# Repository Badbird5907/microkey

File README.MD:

# MicroKey
[Video Demo](https://youtube.com/shorts/Fg3U53FJ8HM)

Firmware can be found [here](https://github.com/Badbird5907/pico-fido-microkey)

This is a FIDO2 security key! It utilizes the RP2350A and [PicoKeys](https://picokeys.com) to implement FIDO2 U2F functionality! Unlike most picokeys, it uses a gold disc like the yubikey to detect touch instead of a tactile button.

I made this project because I saw the RP2350 could be used as a FIDO2 device with firmware like PicoKeys, and I couldn't find a yubikey-like device designed for PicoKeys. All the devices that were used were devboards, with tactile buttons and long USB cables.

# BOM
|Manufacturer                          |Description                                                                                                        |Quantity|Unit Price($)|Ext.Price($)|Link                                                                                                                                    |
|--------------------------------------|-------------------------------------------------------------------------------------------------------------------|--------|-------------|------------|----------------------------------------------------------------------------------------------------------------------------------------|
|UNI-ROYAL(Uniroyal Elec)              |62.5mW Thick Film Resistor 50V ±100ppm/℃ ±1% 1kΩ 0402 Chip Resistor - Surface Mount ROHS                           |100     |0.0006       |0.06        |https://lcsc.com/product-detail/chip-resistor-surface-mount_uni-royal-uniroyal-elec-0402wgf1001tce_C11702.html                          |
|Samsung Electro-Mechanics             |16V 100nF X7R ±10% 0402 Multilayer Ceramic Capacitors MLCC - SMD/SMT ROHS                                          |100     |0.0012       |0.12        |https://lcsc.com/product-detail/multilayer-ceramic-capacitors-mlcc-smd-smt_samsung-electro-mechanics-cl05b104ko5nnnc_C1525.html         |
|FH (Guangdong Fenghua Advanced Tech)  |50V 15pF C0G ±5% 0402 Multilayer Ceramic Capacitors MLCC - SMD/SMT ROHS                                            |100     |0.001        |0.1         |https://lcsc.com/product-detail/multilayer-ceramic-capacitors-mlcc-smd-smt_fh-guangdong-fenghua-advanced-tech-0402cg150j500nt_C1548.html|
|Samsung Electro-Mechanics             |25V 10uF X5R ±10% 0805 Multilayer Ceramic Capacitors MLCC - SMD/SMT ROHS                                           |20      |0.011        |0.22        |https://lcsc.com/product-detail/multilayer-ceramic-capacitors-mlcc-smd-smt_samsung-electro-mechanics-cl21a106kaynnne_C15850.html        |
|Abracon LLC                           |SMD3225-4P Crystals ROHS                                                                                           |1       |0.3731       |0.37        |https://lcsc.com/product-detail/crystals_abracon-llc-abm8-272-t3_C20625731.html                                                         |
|Samsung Electro-Mechanics             |10V 4.7uF X5R ±20% 0402 Multilayer Ceramic Capacitors MLCC - SMD/SMT ROHS                                          |50      |0.0052       |0.26        |https://lcsc.com/product-detail/multilayer-ceramic-capacitors-mlcc-smd-smt_samsung-electro-mechanics-cl05a475mp5nrnc_C23733.html        |
|UNI-ROYAL(Uniroyal Elec)              |62.5mW Thick Film Resistor 50V ±100ppm/℃ ±1% 220Ω 0402 Chip Resistor - Surface Mount ROHS                          |100     |0.0006       |0.06        |https://lcsc.com/product-detail/chip-resistor-surface-mount_uni-royal-uniroyal-elec-0402wgf2200tce_C25091.html                          |
|UNI-ROYAL(Uniroyal Elec)              |62.5mW Thick Film Resistor 50V ±100ppm/℃ ±1% 27Ω 0402 Chip Resistor - Surface Mount ROHS                           |100     |0.0006       |0.06        |https://lcsc.com/product-detail/chip-resistor-surface-mount_uni-royal-uniroyal-elec-0402wgf270jtce_C25100.html                          |
|UNI-ROYAL(Uniroyal Elec)              |62.5mW Thick Film Resistor 50V ±100ppm/℃ ±1% 33Ω 0402 Chip Resistor - Surface Mount ROHS                           |100     |0.0006       |0.06        |https://lcsc.com/product-detail/chip-resistor-surface-mount_uni-royal-uniroyal-elec-0402wgf330jtce_C25105.html                          |
|UNI-ROYAL(Uniroyal Elec)              |62.5mW Thick Film Resistor 50V ±100ppm/℃ ±1% 10kΩ 0402 Chip Resistor - Surface Mount ROHS                          |100     |0.0006       |0.06        |https://lcsc.com/product-detail/chip-resistor-surface-mount_uni-royal-uniroyal-elec-0402wgf1002tce_C25744.html                          |
|UNI-ROYAL(Uniroyal Elec)              |62.5mW Thick Film Resistor 50V ±100ppm/℃ ±1% 5.1kΩ 0402 Chip Resistor - Surface Mount ROHS                         |100     |0.0005       |0.05        |https://lcsc.com/product-detail/chip-resistor-surface-mount_uni-royal-uniroyal-elec-0402wgf5101tce_C25905.html                          |
|Winbond Elec                          |16Mbit SPI 133MHz USON-8-EP(2x3) NOR FLASH ROHS                                                                    |1       |0.6178       |0.62        |https://lcsc.com/product-detail/nor-flash_winbond-elec-w25q16jvuxiq_C2843335.html                                                       |
|Texas Instruments                     |65dB@(100kHz) 300mA Fixed 3.3V Positive 6V SOT-23-5 Voltage Regulators - Linear, Low Drop Out (LDO) Regulators ROHS|5       |0.201        |1.01        |https://lcsc.com/product-detail/voltage-regulators-linear-low-drop-out-ldo-regulators_texas-instruments-tps7a2033pdbvr_C2862740.html    |
|XKB Connection                        |5A 1 12P Male -55℃~+85℃ Type-C SMD USB Connectors ROHS                                                             |1       |1.0428       |1.04        |https://lcsc.com/product-detail/usb-connectors_xkb-connection-u261-121n-4bs2s_C2879827.html                                             |
|Raspberry Pi                          |QFN-60-EP(7x7) Microcontrollers (MCU/MPU/SOC) ROHS                                                                 |1       |1.6544       |1.65        |https://lcsc.com/product-detail/microcontrollers-mcu-mpu-soc_raspberry-pi-rp2350a_C42411118.html                                        |
|Abracon LLC                           |0806 Power Inductors ROHS                                                                                          |5       |0.2584       |`           |https://lcsc.com/product-detail/power-inductors_abracon-llc-aota-b201610s3r3-101-t_C42411119.html                                       |
|Kingbright                            |SMD3528-4P RGB LEDs ROHS                                                                                           |1       |1.6213       |1.62        |https://lcsc.com/product-detail/rgb-leds_kingbright-aaa3528rbgs-08-09_C6851380.html                                                     |
|Shipping                              |                                                                                                                   |        |             |11.71       |                                                                                                                                        |
|Handling Fee                          |                                                                                                                   |        |             |3           |                                                                                                                                        |
|PCB (expensive bc ENIG + edge plating)|                                                                                                                   |        |             |67.28       |                                                                                                                                        |
|Stencil                               |                                                                                                                   |        |             |7.48        |                                                                                                                                        |
|JLC Shipping                          |                                                                                                                   |        |             |7.78        |                                                                                                                                        |
|TOTAL                                 |                                                                                                                   |        |             |104.61      |                                                                                                                                        |

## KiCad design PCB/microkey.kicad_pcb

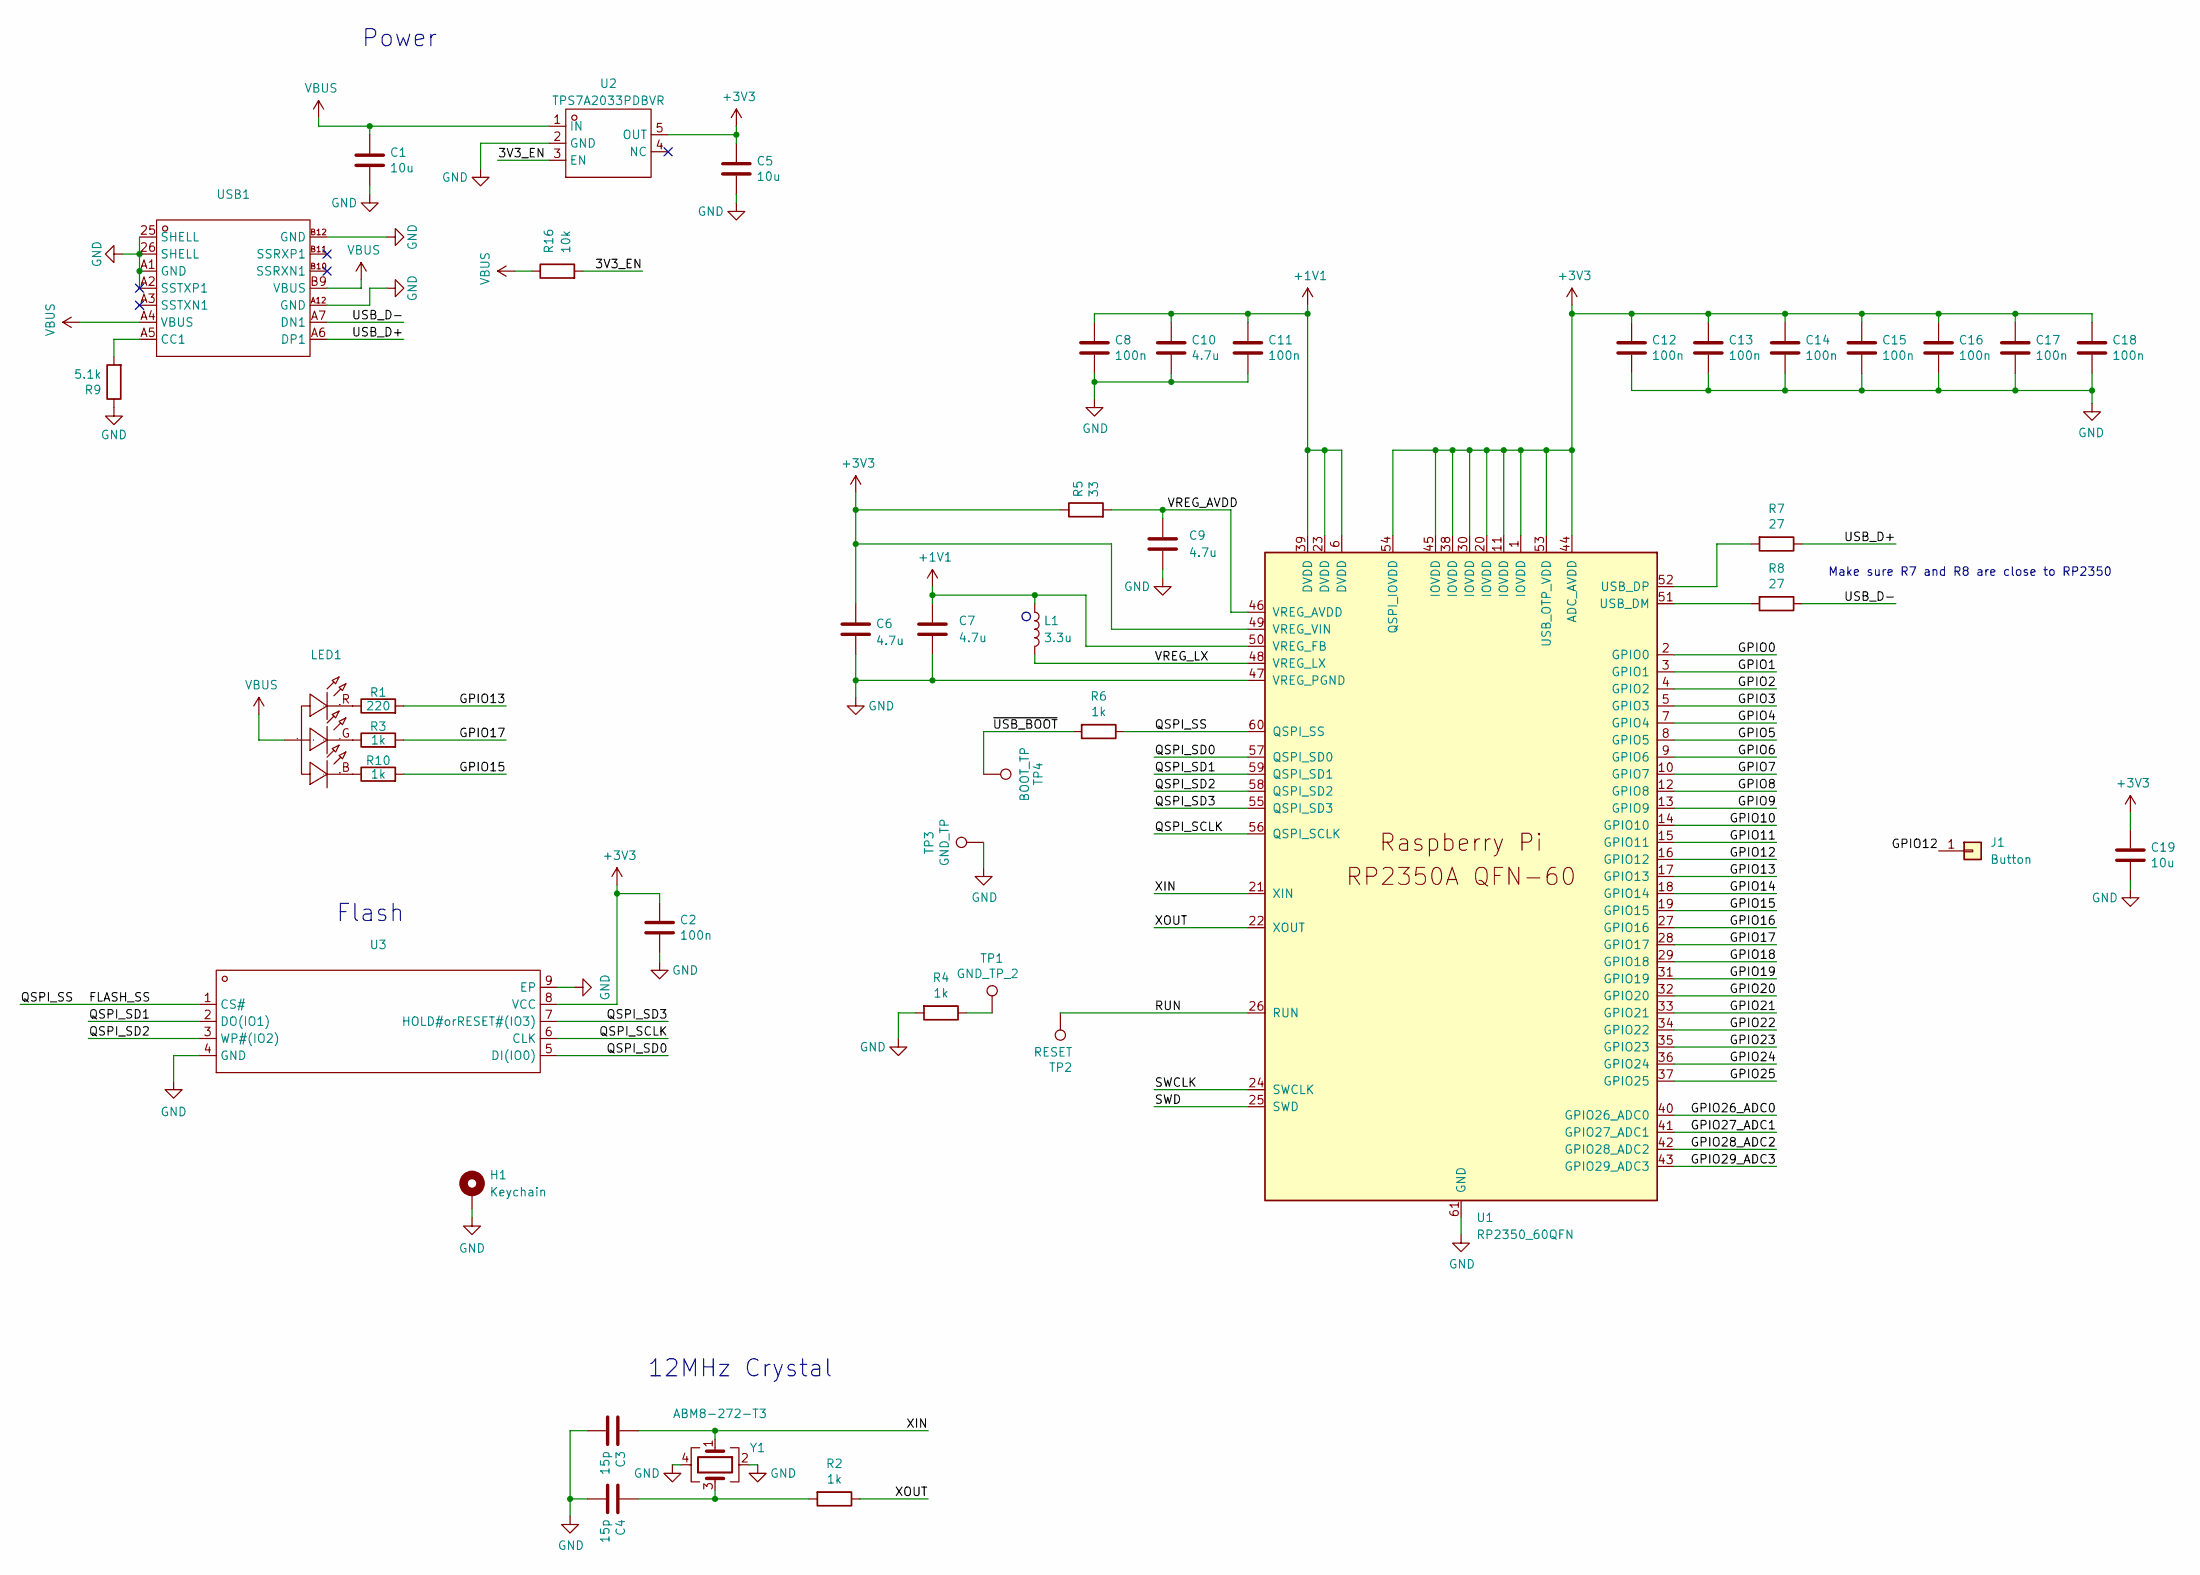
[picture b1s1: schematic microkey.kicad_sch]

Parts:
C1, C5, C19: 10u; C_0805_2012Metric
C2, C8, C11, C12, C13, C14, C15, C16, C17, C18: 100n; C_0402_1005Metric
C3, C4: 15p; C_0402_1005Metric
C6, C7: 4.7u; C_0402_1005Metric_small_pads
C9, C10: 4.7u; C_0402_1005Metric
H1: Keychain
J1: Button
L1: 3.3u; L_pol_2016
LED1: LED-SMD_4P-L3.2-W2.8_XZMDKCBDDG45S-9; Manufacturer Part AAA3528RBGS/08-09; LCSC Part Name AAA3528RBGS/08-09
R1: 220; R_0402_1005Metric
R2, R3, R4, R6, R10: 1k; R_0402_1005Metric
R5: 33; R_0402_1005Metric
R7, R8: 27; R_0402_1005Metric
R9: 5.1k; R_0402_1005Metric
R16: 10k; R_0402_1005Metric
TP1: GND_TP_2; TestPoint_Pad_D1.0mm
TP2: RESET; TestPoint_Pad_D1.0mm
TP3: GND_TP; TestPoint_Pad_D1.0mm
TP4: BOOT_TP; TestPoint_Pad_D1.0mm
U1: RP2350_60QFN; RP2350-QFN-60-1EP_7x7_P0.4mm_EP3.4x3.4mm_ThermalVias
U2: TPS7A2033PDBVR; SOT-23-5_L2.9-W1.6-P0.95-LS2.8-BR; Manufacturer Part TPS7A2033PDBVR; LCSC Part Name 具有高 PSRR 的 300mA、超低噪声、低 IQ、低压降 (LDO) 线性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
U3: USON-8_L3.0-W2.0-P0.50-BL-EP; Manufacturer Part W25Q16JVUXIQ; LCSC Part Name W25Q16JVUXIQ
USB1: USB-C-SMD_U261-121N-4BS2S; Manufacturer Part U261-121N-4BS2S; LCSC Part Name Type-C 公
Y1: ABM8-272-T3; Crystal_SMD_3225-4Pin_3.2x2.5mm

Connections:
+1V1: C7.1, C8.1, C10.1, C11.1, L1.1, U1.6 (DVDD), U1.23 (DVDD), U1.39 (DVDD), U1.50 (VREG_FB)
+3V3: C2.1, C5.1, C6.1, C12.1, C13.1, C14.1, C15.1, C16.1, C17.1, C18.1, C19.1, R5.1, U1.1 (IOVDD), U1.11 (IOVDD), U1.20 (IOVDD), U1.30 (IOVDD), U1.38 (IOVDD), U1.44 (ADC_AVDD), U1.45 (IOVDD), U1.49 (VREG_VIN), U1.53 (USB_OTP_VDD), U1.54 (QSPI_IOVDD), U2.5 (OUT), U3.8 (VCC)
/3V3_EN: R16.2, U2.3 (EN)
/FLASH_SS: R6.1, U1.60 (QSPI_SS), U3.1 (CS#)
/GPIO0: U1.2 (GPIO0)
/GPIO1: U1.3 (GPIO1)
/GPIO2: U1.4 (GPIO2)
/GPIO3: U1.5 (GPIO3)
/GPIO4: U1.7 (GPIO4)
/GPIO5: U1.8 (GPIO5)
/GPIO6: U1.9 (GPIO6)
/GPIO7: U1.10 (GPIO7)
/GPIO8: U1.12 (GPIO8)
/GPIO9: U1.13 (GPIO9)
/GPIO10: U1.14 (GPIO10)
/GPIO11: U1.15 (GPIO11)
/GPIO12: J1.1, U1.16 (GPIO12)
/GPIO13: R1.2, U1.17 (GPIO13)
/GPIO14: U1.18 (GPIO14)
/GPIO15: R10.2, U1.19 (GPIO15)
/GPIO16: U1.27 (GPIO16)
/GPIO17: R3.2, U1.28 (GPIO17)
/GPIO18: U1.29 (GPIO18)
/GPIO19: U1.31 (GPIO19)
/GPIO20: U1.32 (GPIO20)
/GPIO21: U1.33 (GPIO21)
/GPIO22: U1.34 (GPIO22)
/GPIO23: U1.35 (GPIO23)
/GPIO24: U1.36 (GPIO24)
/GPIO25: U1.37 (GPIO25)
/GPIO26_ADC0: U1.40 (GPIO26_ADC0)
/GPIO27_ADC1: U1.41 (GPIO27_ADC1)
/GPIO28_ADC2: U1.42 (GPIO28_ADC2)
/GPIO29_ADC3: U1.43 (GPIO29_ADC3)
/QSPI_SCLK: U1.56 (QSPI_SCLK), U3.6 (CLK)
/QSPI_SD0: U1.57 (QSPI_SD0), U3.5 (DI(IO0))
/QSPI_SD1: U1.59 (QSPI_SD1), U3.2 (DO(IO1))
/QSPI_SD2: U1.58 (QSPI_SD2), U3.3 (WP#(IO2))
/QSPI_SD3: U1.55 (QSPI_SD3), U3.7 (HOLD#orRESET#(IO3))
/RUN: TP2.1, U1.26 (RUN)
/SWCLK: U1.24 (SWCLK)
/SWD: U1.25 (SWD)
/USB_D+: R7.1, USB1.A6 (DP1)
/USB_D-: R8.1, USB1.A7 (DN1)
/VREG_AVDD: C9.1, R5.2, U1.46 (VREG_AVDD)
/VREG_LX: L1.2, U1.48 (VREG_LX)
/XIN: C3.1, U1.21 (XIN), Y1.1
/XOUT: R2.1, U1.22 (XOUT)
/~USB_BOOT: R6.2, TP4.1
GND: C1.2, C2.2, C3.2, C4.2, C5.2, C6.2, C7.2, C8.2, C9.2, C10.2, C11.2, C12.2, C13.2, C14.2, C15.2, C16.2, C17.2, C18.2, C19.2, H1.1, R4.2, R9.1, TP3.1, U1.47 (VREG_PGND), U1.61 (GND), U2.2 (GND), U3.4 (GND), U3.9 (EP), USB1.25 (SHELL), USB1.26 (SHELL), USB1.A1 (GND), USB1.A2 (SSTXP1), USB1.A12 (GND), USB1.B12 (GND), Y1.2, Y1.4
unnamed: C4.1, R2.2, Y1.3
unnamed: LED1.1 (-), R1.1
unnamed: LED1.3 (-), R3.1
unnamed: LED1.4 (-), R10.1
unnamed: R4.1, TP1.1
unnamed: R8.2, U1.51 (USB_DM)
unnamed: R7.2, U1.52 (USB_DP)
unnamed: R9.2, USB1.A5 (CC1)
VBUS: C1.1, LED1.2 (+), R16.1, U2.1 (IN), USB1.A4 (VBUS), USB1.B9 (VBUS)

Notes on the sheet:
Power
Make sure R7 and R8 are close to RP2350
12MHz Crystal
Flash

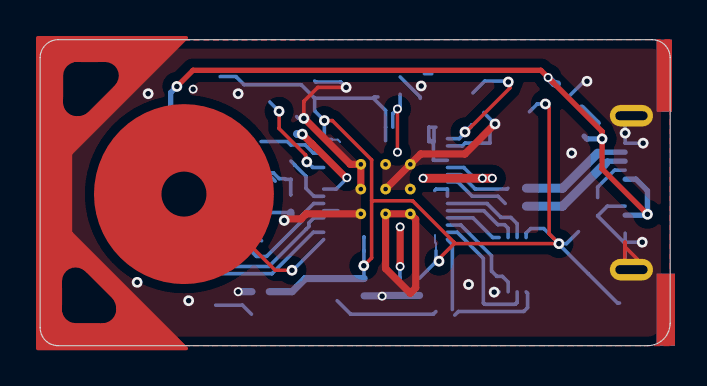
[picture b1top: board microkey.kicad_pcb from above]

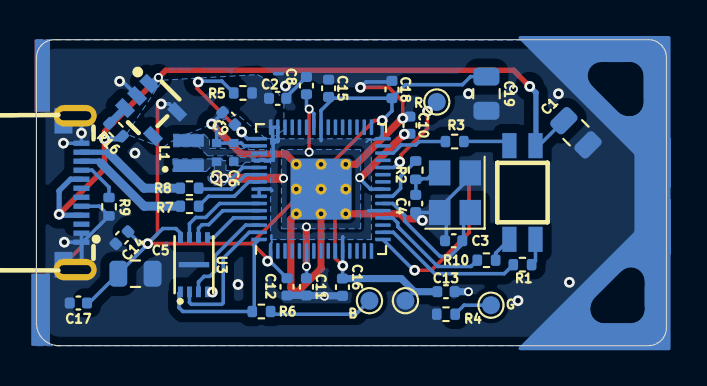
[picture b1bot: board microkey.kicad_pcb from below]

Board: 2 copper layers, 35.0 x 17.0 mm, 43 parts (41 on the bottom side), 31 nets.

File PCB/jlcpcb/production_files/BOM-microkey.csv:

Comment,Designator,Footprint,LCSC,Quantity
1k,"R10,R2,R3,R4,R6",R_0402_1005Metric,C11702,5
100n,"C11,C12,C13,C14,C15,C16,C17,C18,C2,C8",C_0402_1005Metric,C1525,10
15p,"C3,C4",C_0402_1005Metric,C1548,2
10u,"C1,C19,C5",C_0805_2012Metric,C15850,3
ABM8-272-T3,Y1,Crystal_SMD_3225-4Pin_3.2x2.5mm,C20625731,1
4.7u,"C10,C6,C7,C9",C_0402_1005Metric,C23733,4
220,R1,R_0402_1005Metric,C25091,1
27,"R7,R8",R_0402_1005Metric,C25100,2
33,R5,R_0402_1005Metric,C25105,1
10k,R16,R_0402_1005Metric,C25744,1
5.1k,R9,R_0402_1005Metric,C25905,1
~,U3,USON-8_L3.0-W2.0-P0.50-BL-EP,C2843335,1
TPS7A2033PDBVR,U2,SOT-23-5_L2.9-W1.6-P0.95-LS2.8-BR,C2862740,1
~,USB1,USB-C-SMD_U261-121N-4BS2S,C2879827,1
RP2350_60QFN,U1,RP2350-QFN-60-1EP_7x7_P0.4mm_EP3.4x3.4mm_ThermalVias,C42411118,1
3.3u,L1,L_pol_2016,C42411119,1
~,LED1,LED-SMD_4P-L3.2-W2.8_XZMDKCBDDG45S-9,C6851380,1

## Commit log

2025-06-28 readme and bom
2025-06-28 edge plating!!
2025-06-28 readme images
2025-06-30 Update bom and readme
2025-07-23 finish
2025-07-23 update time
2025-09-11 add firmware submodule
2026-01-28 Replace images with updated links
    Updated images in README to new links.
